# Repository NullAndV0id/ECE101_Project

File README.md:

# ECE101_Project
A repository for Uidaho Spring 2019 ECE 101 Project by Team Landhammer

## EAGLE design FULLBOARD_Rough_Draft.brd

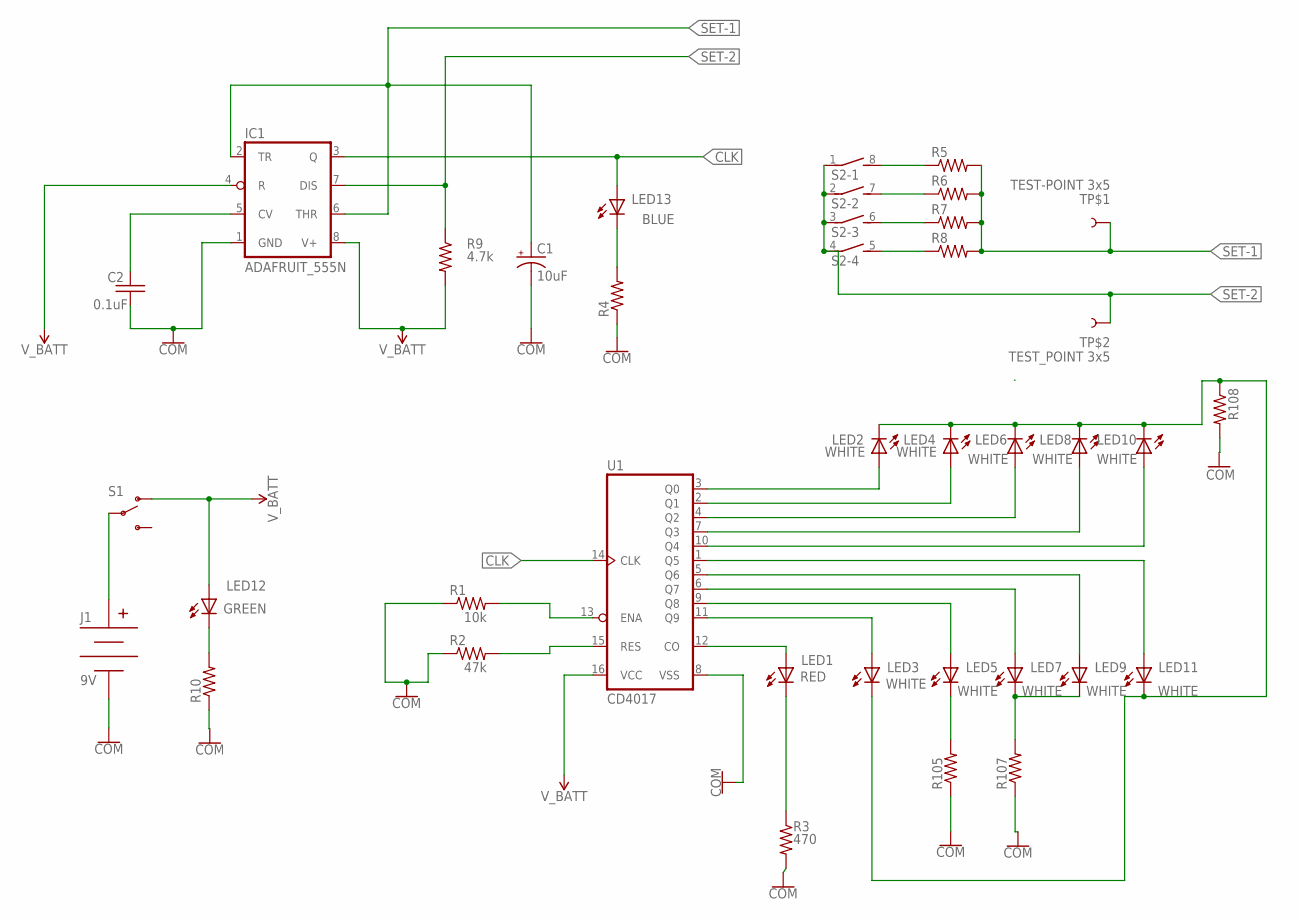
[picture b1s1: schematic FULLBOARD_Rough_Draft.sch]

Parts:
C1: 10uF; ADAFRUIT_E2-5
C2: 0.1uF; ADAFRUIT_C025-025X050
IC1: ADAFRUIT_555N; ADAFRUIT_DIL08-ROUND
J1: 9V; SPARKFUN-CONNECTORS_BC9VPC
LED1: RED; ADAFRUIT_LED5MM
LED2, LED3, LED4, LED5, LED6, LED7, LED8, LED9, LED10, LED11: WHITE; ADAFRUIT_LED5MM
LED12, LED13: ADAFRUIT_LED5MM
R1: 10k; ADAFRUIT_0207/10
R2: 47k; ADAFRUIT_0207/10
R3: 470; ADAFRUIT_0207/10
R4, R5, R6, R7, R8, R10, R105, R107, R108: ADAFRUIT_R-US_0207/10; ADAFRUIT_0207/10
R9: 4.7k; ADAFRUIT_0207/10
S1: SPARKFUN-SWITCHES_SWITCH-SPDT-PTH-11.6X4.0MM; SPARKFUN-SWITCHES_SWITCH_SPDT_PTH_11.6X4.0MM
S2: SWITCH-DIL_DIP04S
TP$1: TEST-POINT 3x5; SPARKFUN-CONNECTORS_PAD.03X.05
TP$2: TEST_POINT 3x5; SPARKFUN-CONNECTORS_PAD.03X.05
U1: CD4017; SPARKFUN-IC-LOGIC_DIP16

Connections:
CLK: IC1.3 (Q), LED13.A, U1.14 (CLK)
COLOR_COMMON: LED1.K (C), R3.1
GND: C1.-, C2.2, IC1.1 (GND), J1.V-, R1.1, R2.1, R3.2, R4.1, R10.1, R105.1, R107.1, R108.2, U1.8 (VSS)
unnamed: R1.2, U1.13 (ENA)
unnamed: R2.2, U1.15 (RES)
unnamed: LED3.A, U1.11 (Q9)
unnamed: LED5.A, U1.9 (Q8)
unnamed: LED12.K (C), R10.2
unnamed: LED7.A, U1.6 (Q7)
unnamed: LED1.A, U1.12 (CO)
unnamed: LED9.A, U1.5 (Q6)
unnamed: LED11.A, U1.1 (Q5)
unnamed: LED2.K (C), LED3.K (C), LED4.K (C), LED6.K (C), LED8.K (C), LED10.K (C), LED11.K (C), R108.1
unnamed: LED2.A, U1.3 (Q0)
unnamed: LED4.A, U1.2 (Q1)
unnamed: LED6.A, U1.4 (Q2)
unnamed: LED8.A, U1.7 (Q3)
unnamed: LED10.A, U1.10 (Q4)
unnamed: LED13.K (C), R4.2
unnamed: LED5.K (C), R105.2
unnamed: LED7.K (C), LED9.K (C), R107.2
unnamed: J1.V+, S1.2
unnamed: R5.1, S2.8 (2)
unnamed: R6.1, S2.7 (2)
unnamed: R7.1, S2.6 (2)
unnamed: R8.1, S2.5 (2)
unnamed: C2.1, IC1.5 (CV)
SET-1: C1.+, IC1.2 (TR), IC1.6 (THR), R5.2, R6.2, R7.2, R8.2, TP$1.P$1
SET-2: IC1.7 (DIS), R9.1, S2.1, S2.2 (1), S2.3 (1), S2.4 (1), TP$2.P$1
V_BATT: IC1.4 (R), IC1.8 (V+), LED12.A, R9.2, S1.1 (O), U1.16 (VCC)

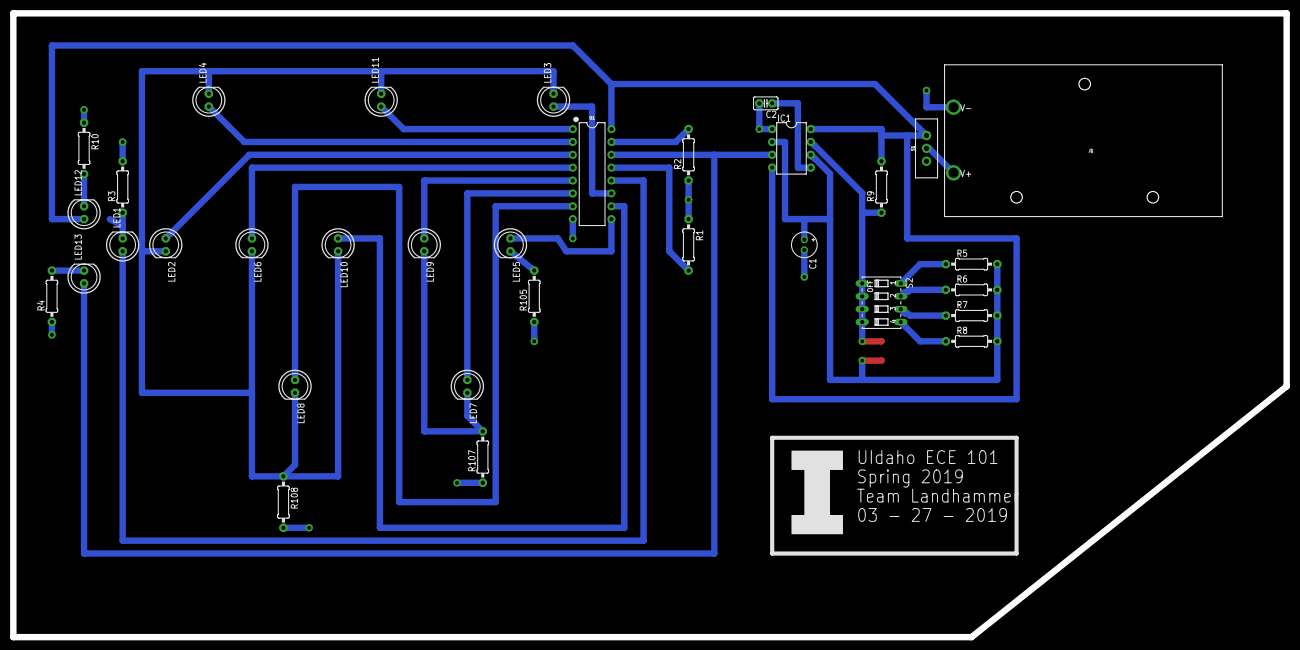
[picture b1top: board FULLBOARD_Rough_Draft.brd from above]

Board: 2 copper layers, 251.5 x 123.2 mm, 35 parts (0 on the bottom side), 30 nets.

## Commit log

2019-03-29 Inital Commit: All material up to this point minus schematic C.
